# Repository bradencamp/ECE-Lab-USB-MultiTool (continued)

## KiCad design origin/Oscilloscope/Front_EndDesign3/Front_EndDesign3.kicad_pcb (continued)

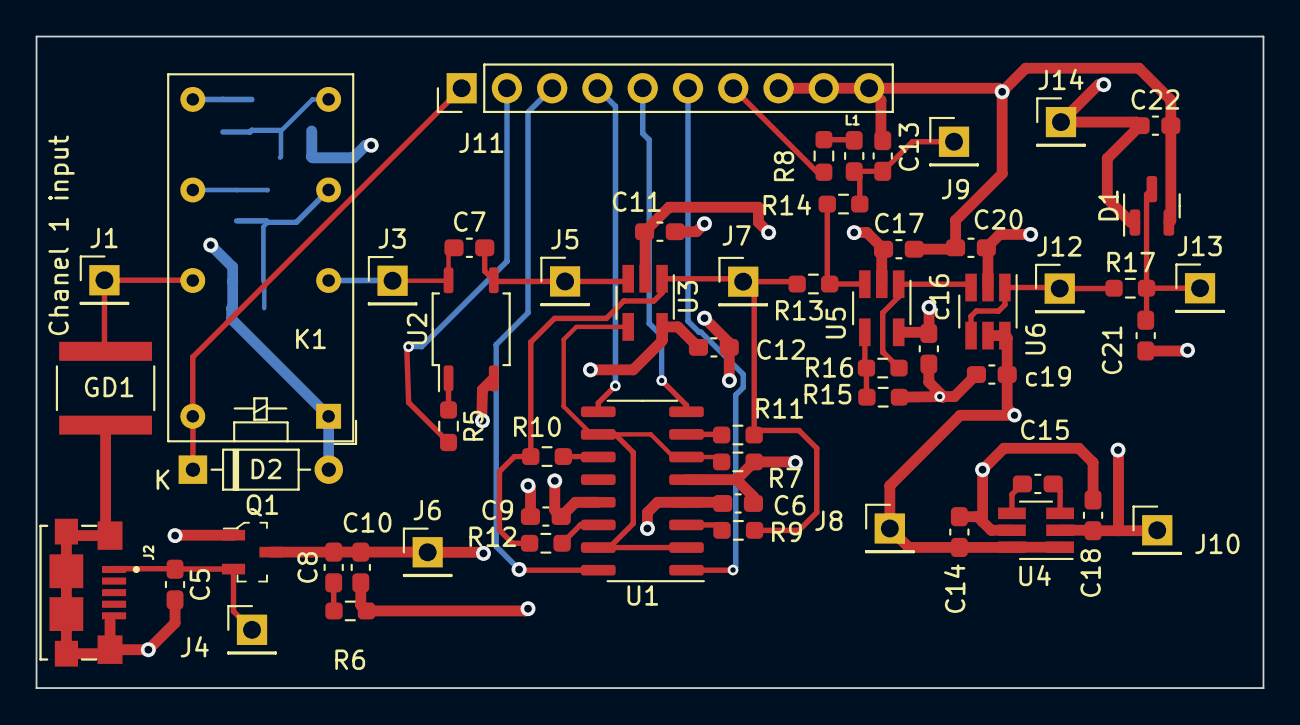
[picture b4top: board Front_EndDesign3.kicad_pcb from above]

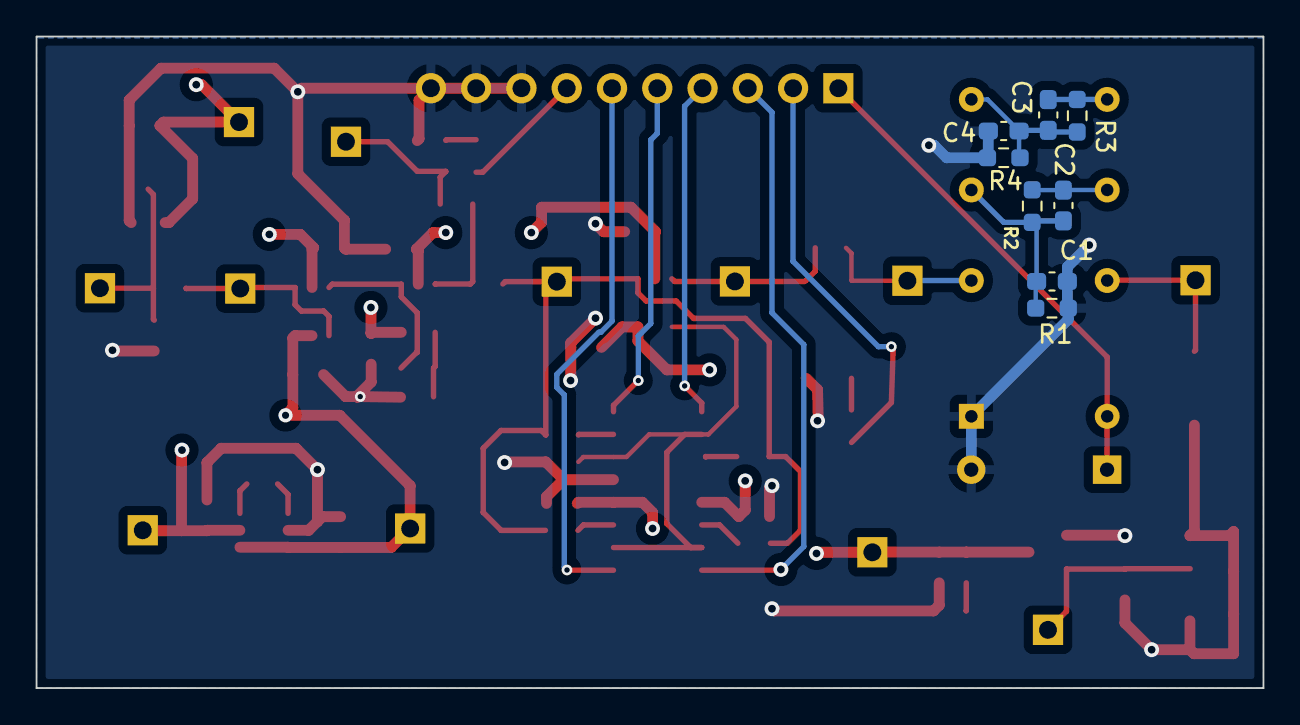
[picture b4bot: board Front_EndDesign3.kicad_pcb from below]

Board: 4 copper layers, 68.8 x 36.6 mm, 65 parts (8 on the bottom side), 36 nets.

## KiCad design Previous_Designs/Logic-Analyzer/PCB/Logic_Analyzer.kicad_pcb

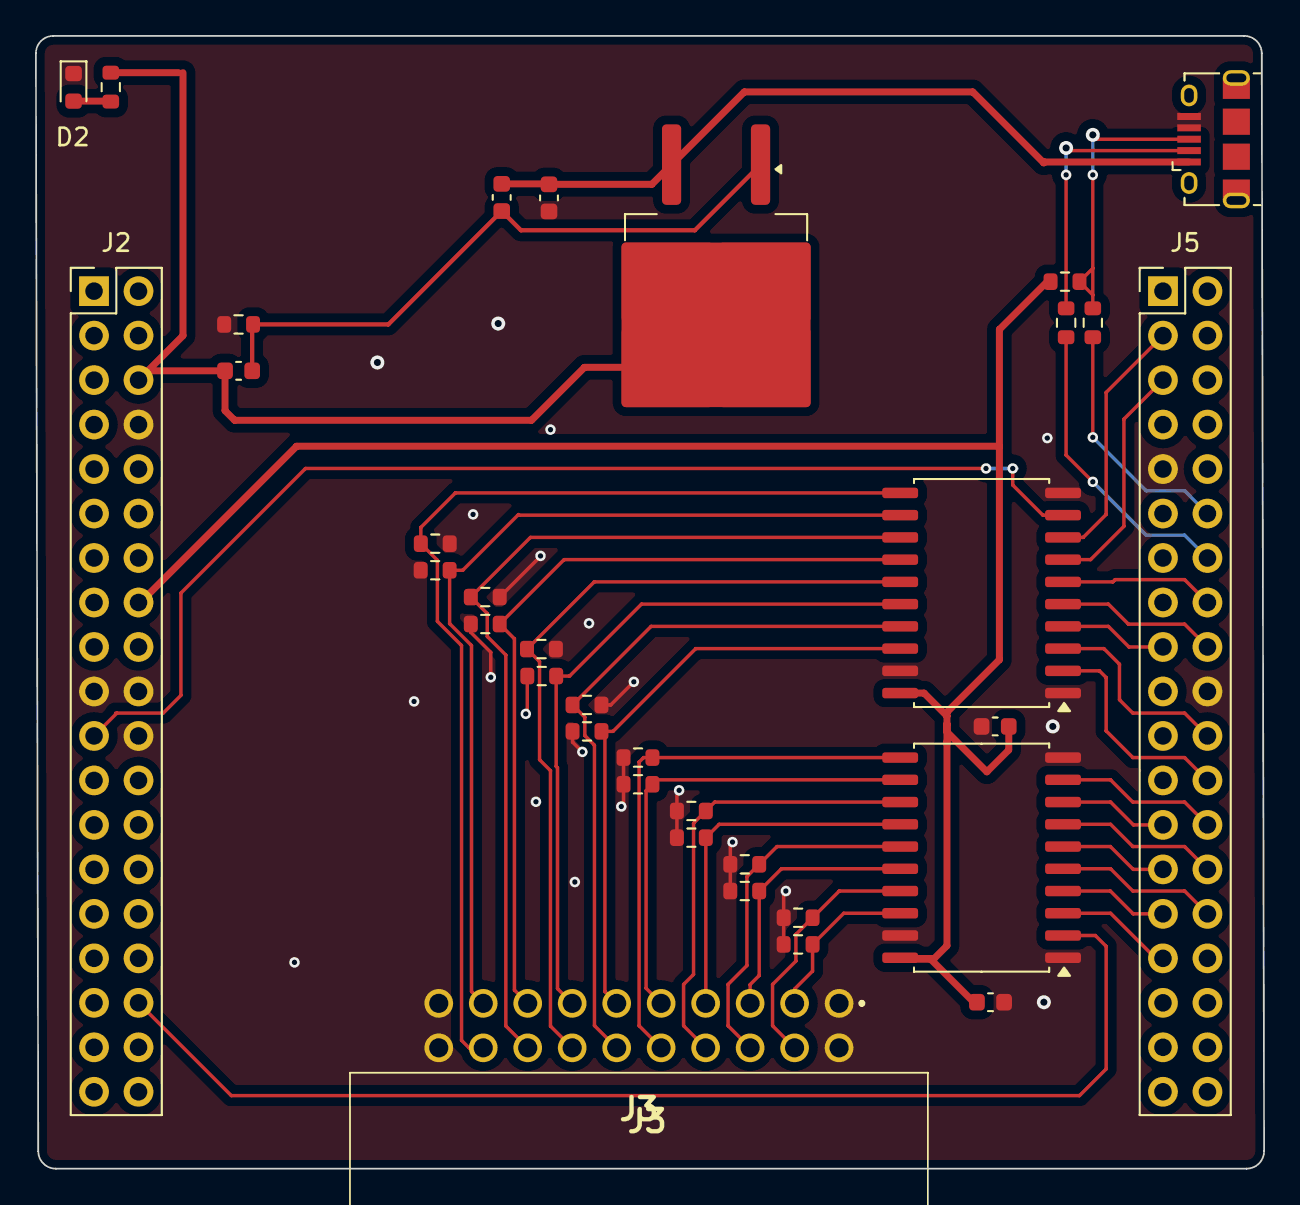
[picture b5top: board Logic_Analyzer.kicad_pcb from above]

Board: 2 copper layers, 70.1 x 64.7 mm, 34 parts (0 on the bottom side), 42 nets.

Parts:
C1, C2, C4, C5: 100nF; C_0603_1608Metric
C3: 1uF; C_0603_1608Metric
D2: LED; LED_0603_1608Metric
J1: USB Micro; USB_Micro-B_Amphenol_10118194_Horizontal
J2: nuc303_LEFT; PinSocket_2x19_P2.54mm_Vertical
J3: 30320-5002HB; 303205002HB
J5: nuc303_RIGHT; PinSocket_2x19_P2.54mm_Vertical
Q2: PMOS; TO-263-2
R1, R6, R7, R8, R9, R10, R11, R12, R13, R14, R15, R16, R17, R18, R19, R20, R21: 1M; R_0603_1608Metric
R2, R4: 22; R_0603_1608Metric
R3: 1k; R_0603_1608Metric
R5: 1.5k; R_0603_1608Metric
U1, U3: 74HC245N; SOIC-20W_7.5x12.8mm_P1.27mm

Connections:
+3V3: C4.1, C5.2, J2.16 (3V3), R5.2, U1.20 (VCC), U3.20 (VCC)
+5V: C2.1, J2.6 (E5V), Q2.2 (G), R3.1
/D+: J1.3 (D+), R2.2, R5.1
/D-: J1.2 (D-), R4.1
/PB0: J2.34 (PB0), U1.2 (A0)
/PB1: J5.24 (PB1), U3.2 (A0)
/PB2: J5.22 (PB2), U3.3 (A1)
/PB3: J5.31 (PB3), U1.3 (A1)
/PB4: J5.27 (PB4), U1.6 (A4)
/PB5: J5.29 (PB5), U1.4 (A2)
/PB6: J5.17 (PB6), U3.4 (A2)
/PB7: J2.21 (PB7), U3.9 (A7)
/PB8: J5.3 (PB8), U3.8 (A6)
/PB9: J5.5 (PB9), U3.7 (A5)
/PB10: J5.25 (PB10), U1.8 (A6)
/PB11: J5.18 (PB11), U3.5 (A3)
/PB12: J5.16 (PB12), U3.6 (A4)
/PB13: J5.30 (PB13), U1.5 (A3)
/PB14: J5.28 (PB14), U1.7 (A5)
/PB15: J5.26 (PB15), U1.9 (A7)
/VBUS: C1.1, C3.1, J1.1 (VBUS), Q2.3 (S)
GND: C3.2, C4.2, C5.1, D2.1 (K), J1.4 (GND), J1.5 (Shield), J2.8 (GND), J2.19 (GND), J2.20 (GND), J2.22 (GND), J3.1, J3.2, J3.19, J3.20, J5.9 (GND), J5.20 (GND), R1.2, R6.1, R7.2, R8.1, R9.2, R10.1, R11.2, R12.2, R13.1, R14.2, R15.2, R16.2, R17.2, R18.1, R19.1, R20.1, R21.1, U1.1 (DIR), U1.10 (GND), U1.19 (~OE), U3.1 (DIR), U3.10 (GND), U3.19 (~OE)
unnamed: D2.2 (A), R3.2
unnamed: J5.14 (PA11), R4.2
unnamed: J5.12 (PA12), R2.1
unnamed: C1.2, C2.2, Q2.1 (D), R1.1
unnamed: J3.3, R14.1, U1.18 (B0)
unnamed: J3.4, R18.2, U1.17 (B1)
unnamed: J3.5, R15.1, U1.16 (B2)
unnamed: J3.6, R19.2, U1.15 (B3)
unnamed: J3.7, R16.1, U1.14 (B4)
unnamed: J3.8, R21.2, U1.13 (B5)
unnamed: J3.9, R17.1, U1.12 (B6)
unnamed: J3.10, R20.2, U1.11 (B7)
unnamed: J3.11, R12.1, U3.18 (B0)
unnamed: J3.12, R8.2, U3.17 (B1)
unnamed: J3.13, R9.1, U3.16 (B2)
unnamed: J3.14, R13.2, U3.15 (B3)
unnamed: J3.15, R11.1, U3.14 (B4)
unnamed: J3.16, R10.2, U3.13 (B5)
unnamed: J3.17, R7.1, U3.12 (B6)
unnamed: J3.18, R6.2, U3.11 (B7)

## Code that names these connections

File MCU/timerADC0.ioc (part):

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Mcu.Name=STM32H563ZITx
Mcu.Package=LQFP144
Mcu.UserName=STM32H563ZITx
PA0.Signal=ADCx_INP0
PA1.GPIOParameters=GPIO_Speed,GPIO_PuPd,GPIO_Label,GPIO_Mode
PA1.GPIO_Label=RMII_REF_CLK
PA1.GPIO_Mode=GPIO_MODE_AF_PP
PA1.GPIO_PuPd=GPIO_NOPULL
PA1.GPIO_Speed=GPIO_SPEED_FREQ_LOW
PA1.Signal=ETH_REF_CLK
PA11.GPIOParameters=GPIO_Label
PA11.GPIO_Label=USB_FS_N
PA11.Mode=Device
PA11.Signal=USB_DM
PA12.GPIOParameters=GPIO_Label
PA12.GPIO_Label=USB_FS_P
PA12.Mode=Device
PA12.Signal=USB_DP
PA13(JTMS/SWDIO).GPIOParameters=GPIO_Label
PA13(JTMS/SWDIO).GPIO_Label=SWDIO
PA13(JTMS/SWDIO).Signal=DEBUG_JTMS-SWDIO
PA14(JTCK/SWCLK).GPIOParameters=GPIO_Label
PA14(JTCK/SWCLK).GPIO_Label=SWCLK
PA14(JTCK/SWCLK).Signal=DEBUG_JTCK-SWCLK
PA15(JTDI).GPIOParameters=GPIO_Label
PA15(JTDI).GPIO_Label=T_JTDI
PA15(JTDI).Signal=DEBUG_JTDI
PA2.GPIOParameters=GPIO_Speed,GPIO_PuPd,GPIO_Label,GPIO_Mode
PA2.GPIO_Label=RMII_MDIO
PA2.GPIO_Mode=GPIO_MODE_AF_PP
PA2.GPIO_PuPd=GPIO_NOPULL
PA2.GPIO_Speed=GPIO_SPEED_FREQ_LOW
PA2.Signal=ETH_MDIO
PA4.Signal=COMP_DAC11_group
PA5.Signal=COMP_DAC12_group
PA6.Signal=ADCx_INP3
PA7.Signal=ETH_CRS_DV
PA9.GPIOParameters=GPIO_Label
PA9.GPIO_Label=UCDP_DBn
PA9.Signal=UCPD1_DB1
PB0.Signal=GPIO_Output
PB10.GPIOParameters=GPIO_Label
PB10.GPIO_Label=CH2_1\:5_AMP
PB10.Signal=GPIO_Output
PB13.GPIOParameters=GPIO_Label
PB13.GPIO_Label=UCPD_CC1
PB13.Signal=UCPD1_CC1
PB14.GPIOParameters=GPIO_Label
PB14.GPIO_Label=UCPD_CC2
PB14.Signal=UCPD1_CC2
PB15.GPIOParameters=GPIO_Speed,GPIO_PuPd,GPIO_Label,GPIO_Mode
PB15.GPIO_Label=RMII_TXD1
PB15.GPIO_Mode=GPIO_MODE_AF_PP
PB15.GPIO_PuPd=GPIO_NOPULL
PB15.GPIO_Speed=GPIO_SPEED_FREQ_LOW
PB15.Signal=ETH_TXD1
PB3(JTDO/TRACESWO).GPIOParameters=GPIO_Label
PB3(JTDO/TRACESWO).GPIO_Label=SWO
PB3(JTDO/TRACESWO).Signal=DEBUG_JTDO-SWO
PB6.GPIOParameters=GPIO_Label
PB6.GPIO_Label=ARD_D1_TX
PB6.Signal=LPUART1_TX
PB7.GPIOParameters=GPIO_Label
PB7.GPIO_Label=ARD_D0_RX
PB7.Signal=LPUART1_RX
PC1.GPIOParameters=GPIO_Speed,GPIO_PuPd,GPIO_Label,GPIO_Mode
PC1.GPIO_Label=RMII_MDC
PC1.GPIO_Mode=GPIO_MODE_AF_PP
PC1.GPIO_PuPd=GPIO_NOPULL
PC1.GPIO_Speed=GPIO_SPEED_FREQ_LOW
PC1.Signal=ETH_MDC
PC10.GPIOParameters=GPIO_Label
PC10.GPIO_Label=CH1_1\:1_AMP
PC10.Signal=GPIO_Output
PC11.GPIOParameters=GPIO_Label
PC11.GPIO_Label=CH1_1\:2.5_AMP
PC11.Signal=GPIO_Output
PC12.GPIOParameters=GPIO_Label
PC12.GPIO_Label=CH1_1\:5_AMP
PC12.Signal=GPIO_Output
PC13.Signal=GPIO_Input
PC14-OSC32_IN(OSC32_IN).Mode=LSE-External-Oscillator
PC14-OSC32_IN(OSC32_IN).Signal=RCC_OSC32_IN
PC15-OSC32_OUT(OSC32_OUT).Mode=LSE-External-Oscillator
PC15-OSC32_OUT(OSC32_OUT).Signal=RCC_OSC32_OUT
PC4.GPIOParameters=GPIO_Speed,GPIO_PuPd,GPIO_Label,GPIO_Mode
PC4.GPIO_Label=RMII_RXD0
PC4.GPIO_Mode=GPIO_MODE_AF_PP
PC4.GPIO_PuPd=GPIO_NOPULL
PC4.GPIO_Speed=GPIO_SPEED_FREQ_LOW
PC4.Signal=ETH_RXD0
PC5.GPIOParameters=GPIO_Speed,GPIO_PuPd,GPIO_Label,GPIO_Mode
PC5.GPIO_Label=RMII_RXD1
PC5.GPIO_Mode=GPIO_MODE_AF_PP
PC5.GPIO_PuPd=GPIO_NOPULL
PC5.GPIO_Speed=GPIO_SPEED_FREQ_LOW
PC5.Signal=ETH_RXD1
PC6.Signal=S_TIM3_CH1
PC7.Signal=S_TIM3_CH2
PC8.Signal=S_TIM8_CH3
PD0.GPIOParameters=GPIO_Label
PD0.GPIO_Label=CH1_1\:10_AMP
PD0.Signal=GPIO_Output
PD1.GPIOParameters=GPIO_Label
PD1.GPIO_Label=CH1_ATTENUATOR
PD1.Signal=GPIO_Output
PD2.GPIOParameters=GPIO_Label
PD2.GPIO_Label=CH1_AC/DC
PD2.Signal=GPIO_Output
PD4.GPIOParameters=GPIO_Label
PD4.GPIO_Label=External LED0
PD4.Signal=GPIO_Output
PD5.GPIOParameters=GPIO_Label
PD5.GPIO_Label=External LED1
PD5.Signal=GPIO_Output
PD6.GPIOParameters=GPIO_Label
PD6.GPIO_Label=External LED2
PD6.Signal=GPIO_Output
PD7.GPIOParameters=GPIO_Label
PD7.GPIO_Label=External LED3
PD7.Signal=GPIO_Output
PD8.Signal=USART3_TX
PD9.Signal=USART3_RX
PE11.Signal=S_TIM1_CH2
PE12.GPIOParameters=GPIO_Label
PE12.GPIO_Label=GAIN_C1
PE12.Signal=GPIO_Output
PE13.GPIOParameters=GPIO_Label
PE13.GPIO_Label=GAIN_C0
PE13.Signal=GPIO_Output
PE14.GPIOParameters=GPIO_Label
PE14.GPIO_Label=CH2_1\:1_AMP
PE14.Signal=GPIO_Output
PE15.GPIOParameters=GPIO_Label
PE15.GPIO_Label=CH2_1\:2.5_AMP
PE15.Signal=GPIO_Output
PE2.GPIOParameters=GPIO_Label
PE2.GPIO_Label=TRACE_CK
PE2.Signal=DEBUG_TRACECLK
PE3.GPIOParameters=GPIO_Label
PE3.GPIO_Label=TRACE_D0
PE3.Signal=DEBUG_TRACED0
PE4.GPIOParameters=GPIO_Label
PE4.GPIO_Label=TRACE_D1
PE4.Signal=DEBUG_TRACED1
PE5.GPIOParameters=GPIO_Label
PE5.GPIO_Label=TRACE_D2
PE5.Signal=DEBUG_TRACED2
PE6.GPIOParameters=GPIO_Label
PE6.GPIO_Label=TRACE_D3
PE6.Signal=DEBUG_TRACED3
PE7.GPIOParameters=GPIO_Label
PE7.GPIO_Label=CH2_AC/DC
PE7.Signal=GPIO_Output
PE9.Signal=S_TIM1_CH1
PF0.Signal=GPIO_Input
PF1.Signal=GPIO_Input
PF10.Signal=GPIO_Input
PF11.Signal=GPIO_Input
PF12.Signal=GPIO_Input
PF13.Signal=GPIO_Input
PF14.Signal=GPIO_Input
PF15.Signal=GPIO_Input
PF2.Signal=GPIO_Input
PF3.Signal=GPIO_Input
PF4.Signal=GPIO_Input
PF5.Signal=GPIO_Input
PF6.Signal=GPIO_Input
PF7.Signal=GPIO_Input
PF8.Signal=GPIO_Input
PF9.Signal=GPIO_Input
PG0.Signal=GPIO_Output
PG1.GPIOParameters=GPIO_Label
PG1.GPIO_Label=CH2_ATTENUATOR
PG1.Signal=GPIO_Output
PG11.GPIOParameters=GPIO_Speed,GPIO_PuPd,GPIO_Label,GPIO_Mode
PG11.GPIO_Label=RMII_TXT_EN
PG11.GPIO_Mode=GPIO_MODE_AF_PP
PG11.GPIO_PuPd=GPIO_NOPULL
PG11.GPIO_Speed=GPIO_SPEED_FREQ_LOW
PG11.Signal=ETH_TX_EN
PG13.GPIOParameters=GPIO_Speed,GPIO_PuPd,GPIO_Label,GPIO_Mode
PG13.GPIO_Label=RMI_TXD0
PG13.GPIO_Mode=GPIO_MODE_AF_PP
PG13.GPIO_PuPd=GPIO_NOPULL
PG13.GPIO_Speed=GPIO_SPEED_FREQ_LOW
PG13.Signal=ETH_TXD0
PG4.Signal=GPIO_Output
PG7.GPIOParameters=GPIO_Label
PG7.GPIO_Label=UCPD_FLT
PG7.Signal=GPXTI7
PH0-OSC_IN(PH0).GPIOParameters=GPIO_Label
PH0-OSC_IN(PH0).GPIO_Label=STLK_MCO
PH0-OSC_IN(PH0).Mode=HSE-External-Clock-Source
PH0-OSC_IN(PH0).Signal=RCC_OSC_IN
RCC.HSE_VALUE=8000000
RCC.SYSCLKFreq_VALUE=250000000
RCC.SYSCLKSource=RCC_SYSCLKSOURCE_PLLCLK
board=NUCLEO-H563ZI
boardIOC=true

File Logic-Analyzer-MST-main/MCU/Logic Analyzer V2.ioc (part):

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Mcu.Name=STM32F303R(D-E)Tx
Mcu.Package=LQFP64
Mcu.UserName=STM32F303RETx
PA11.Mode=Device
PA11.Signal=USB_DM
PA12.Mode=Device
PA12.Signal=USB_DP
PA13.GPIOParameters=GPIO_Label
PA13.GPIO_Label=TMS
PA13.Mode=Serial_Wire
PA13.Signal=SYS_JTMS-SWDIO
PA14.GPIOParameters=GPIO_Label
PA14.GPIO_Label=TCK
PA14.Mode=Serial_Wire
PA14.Signal=SYS_JTCK-SWCLK
PA5.GPIOParameters=GPIO_Speed,GPIO_PuPd,GPIO_Label,GPIO_Mode
PA5.GPIO_Label=LD2 [Green Led]
PA5.GPIO_Mode=GPIO_MODE_OUTPUT_PP
PA5.GPIO_PuPd=GPIO_NOPULL
PA5.GPIO_Speed=GPIO_SPEED_FREQ_LOW
PA5.Signal=GPIO_Output
PB0.Signal=GPIO_Input
PB1.Signal=GPIO_Input
PB10.Signal=GPIO_Input
PB11.Signal=GPIO_Input
PB12.Signal=GPIO_Input
PB13.Signal=GPIO_Input
PB14.Signal=GPIO_Input
PB15.Signal=GPIO_Input
PB2.Signal=GPIO_Input
PB3.Signal=GPIO_Input
PB4.Signal=GPIO_Input
PB5.Signal=GPIO_Input
PB6.Signal=GPIO_Input
PB7.Signal=GPIO_Input
PB8.Signal=GPIO_Input
PB9.Signal=GPIO_Input
PC13.GPIOParameters=GPIO_Label,GPIO_ModeDefaultEXTI
PC13.GPIO_Label=B1 [Blue PushButton]
PC13.GPIO_ModeDefaultEXTI=GPIO_MODE_IT_FALLING
PC13.Signal=GPXTI13
PC14-OSC32_IN.Mode=LSE-External-Oscillator
PC14-OSC32_IN.Signal=RCC_OSC32_IN
PC15-OSC32_OUT.Mode=LSE-External-Oscillator
PC15-OSC32_OUT.Signal=RCC_OSC32_OUT
PF0-OSC_IN.Mode=HSE-External-Oscillator
PF0-OSC_IN.Signal=RCC_OSC_IN
PF1-OSC_OUT.Mode=HSE-External-Oscillator
PF1-OSC_OUT.Signal=RCC_OSC_OUT
RCC.HSE_VALUE=8000000
RCC.SYSCLKFreq_VALUE=72000000
RCC.SYSCLKSourceVirtual=RCC_SYSCLKSOURCE_PLLCLK
board=NUCLEO-F303RE
boardIOC=true

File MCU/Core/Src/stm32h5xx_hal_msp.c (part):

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
    __HAL_RCC_GPIOA_CLK_ENABLE();
    /**ADC1 GPIO Configuration
    PA0     ------> ADC1_INP0
    */
    GPIO_InitStruct.Pin = GPIO_PIN_0;
    GPIO_InitStruct.Mode = GPIO_MODE_ANALOG;
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
    __HAL_RCC_GPIOA_CLK_ENABLE();
    /**ADC2 GPIO Configuration
    PA6     ------> ADC2_INP3
    */
    GPIO_InitStruct.Pin = GPIO_PIN_6;
    GPIO_InitStruct.Mode = GPIO_MODE_ANALOG;
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    }

    /**ADC1 GPIO Configuration
    PA0     ------> ADC1_INP0
    */
    HAL_GPIO_DeInit(GPIOA, GPIO_PIN_0);

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    }

    /**ADC2 GPIO Configuration
    PA6     ------> ADC2_INP3
    */
    HAL_GPIO_DeInit(GPIOA, GPIO_PIN_6);

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
    __HAL_RCC_GPIOA_CLK_ENABLE();
    /**DAC1 GPIO Configuration
    PA4     ------> DAC1_OUT1
    PA5     ------> DAC1_OUT2
    */
    GPIO_InitStruct.Pin = GPIO_PIN_4|GPIO_PIN_5;
    GPIO_InitStruct.Mode = GPIO_MODE_ANALOG;
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    __HAL_RCC_DAC1_CLK_DISABLE();

    /**DAC1 GPIO Configuration
    PA4     ------> DAC1_OUT1
    PA5     ------> DAC1_OUT2
    */
    HAL_GPIO_DeInit(GPIOA, GPIO_PIN_4|GPIO_PIN_5);

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  /* USER CODE END TIM1_MspPostInit 0 */
    __HAL_RCC_GPIOE_CLK_ENABLE();
    /**TIM1 GPIO Configuration
    PE9     ------> TIM1_CH1
    PE11     ------> TIM1_CH2
    */
    GPIO_InitStruct.Pin = GPIO_PIN_9|GPIO_PIN_11;
    GPIO_InitStruct.Mode = GPIO_MODE_AF_PP;
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
    __HAL_RCC_GPIOC_CLK_ENABLE();
    /**TIM3 GPIO Configuration
    PC6     ------> TIM3_CH1
    PC7     ------> TIM3_CH2
    */
    GPIO_InitStruct.Pin = GPIO_PIN_6|GPIO_PIN_7;
    GPIO_InitStruct.Mode = GPIO_MODE_AF_PP;
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
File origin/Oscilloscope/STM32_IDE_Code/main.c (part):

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  GPIO_InitStruct.Pull = GPIO_NOPULL;
  HAL_GPIO_Init(B1_GPIO_Port, &GPIO_InitStruct);

  /*Configure GPIO pins : LD2_Pin PA8 PA9 PA10 */
  GPIO_InitStruct.Pin = LD2_Pin|GPIO_PIN_8|GPIO_PIN_9|GPIO_PIN_10;
  GPIO_InitStruct.Mode = GPIO_MODE_OUTPUT_PP;
  GPIO_InitStruct.Pull = GPIO_NOPULL;
  GPIO_InitStruct.Speed = GPIO_SPEED_FREQ_LOW;
  HAL_GPIO_Init(GPIOA, &GPIO_InitStruct);

  /*Configure GPIO pins : PB10 PB4 */
  GPIO_InitStruct.Pin = GPIO_PIN_10|GPIO_PIN_4;
  GPIO_InitStruct.Mode = GPIO_MODE_OUTPUT_PP;
  GPIO_InitStruct.Pull = GPIO_NOPULL;
  GPIO_InitStruct.Speed = GPIO_SPEED_FREQ_LOW;
  HAL_GPIO_Init(GPIOB, &GPIO_InitStruct);

  /*Configure GPIO pin : PC7 */
  GPIO_InitStruct.Pin = GPIO_PIN_7;
  GPIO_InitStruct.Mode = GPIO_MODE_OUTPUT_PP;
  GPIO_InitStruct.Pull = GPIO_NOPULL;
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
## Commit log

2024-09-12 Updated GUI readme syntax
2024-09-23 Code cleanup
2024-10-18 Figuring out USB
    Have to use ThreadX RTOS and USBX to implement USB function. This is just the first way I got working.
2024-10-18 USB attempt
    Have to use ThreadX RTOS and USBX.
2024-10-18 Initial GUI
2024-10-23 2 ADCs using DMA to transfer over USART
    Just a test
2024-10-23 Moved layouts into individual functions, collapsed AWG panel
2024-10-29 Labeled text widget and initial graph
2024-10-29 Starting PCB schematics
2024-10-31 Bare Metal USB
    spams "hello" on COM12. Cannot use ICACHE.
2024-10-31 GUI layout and updating random graph
2024-11-01 added missing GND
2024-11-01 testing new branch
2024-11-01 inital branch
2024-11-05 DAC + USB
    Based on previous team's work.
2024-11-06 awg checkboxes work with live plotting, but need to fix waveform positioning for displaying individual chanels. Placement correct for simultaneous channels
2024-11-12 run/stop button works, updated trigger mode options
2024-11-13 minor changes & added comments. still trying to get scope channel checkboxes working
2024-11-13 AWG control for ch1 and time divs. Also now working with numpy over python lists
2024-11-13 minor changes
2024-11-14 combined brach code into 1 file. added ch2 sine wave, removed temperature test wave
2024-11-15 added 8 example square waves for logic analyzer. checkboxes for analyzer & scope buggy, working on fixing
2024-11-16 Starting PCB layout
2024-11-18 Finished PCB traces
2024-12-03 Waveform Type selector completed
2024-12-04 Simple serial connection and color correction
2024-12-04 Update PCB
2024-12-07 began merging handlers for boxes, buttons, plot, user input; added ch2 for all; minor text/design changes; will update colors
2024-12-17 fixed ch2 awg amplitude input box. live input for amp. now works for both channels & plot autoscales correctly
2024-12-17 removed old commit comments
2025-01-06 Updated PCB Layout 1.2
2025-01-07 Revert "Updated PCB Layout 1.2"
    This reverts commit d1c1e699940df8d57e662003311594f1cc4f50c6.
    Reverting broken commit
2025-01-07 Moving files to where they should be
2025-01-15 interim update (not done)
2025-01-17 Routed revised PCB
2025-01-17 fix name for PWR_FLAG
2025-01-24 current local copy. will discuss w/ erick today
2025-02-05 update components and wiring
2025-02-11 change USB design and MCU
2025-02-11 AWG working
    Use the AWG team's GUI to interact with the MCU.
2025-02-11 Add files via upload
    Used AWG team GUI to test. For AWG GUI VID and PID need to be modified in connection.py to establish connection. (port.vid == 1155 and port.pid == 22352)
2025-02-12 Modified to function simmilarly to amai8 branch.
2025-02-16 update MCU and USB, fix some footprints
2025-02-18 modify MCU and name tags
2025-02-19 add usb protection
2025-02-19 combined eorella & amai8 latest commits
2025-02-21 add NRST button and change MCU pins as latest
2025-02-23 Fixed up footprints
2025-02-23 Added files to gitignore
2025-02-23 Added file to gitignore
2025-02-23 Rm old libraries
2025-02-23 Started adding 20pin
2025-02-26 Began on logic analyizer. Also added csv of sample i2c connection
2025-02-26 add Logic Analyzer and finish pins
    Add Logic Analyzer. Add separate pins to 20 pins input(logic and scope) and 4 pins output(AWG). Add 4 programing pins.
2025-02-26 minor fixes
2025-02-26 footprint with minor fixes
2025-02-28 updated csv functionality
2025-03-01 rearrange logic pins, connectors, fix some name tags
2025-03-01 Updated schematic
2025-03-01 Update logic analyzer schematic
2025-03-01 change 3.3V regulator
    Using ST1L05APU33R instead of ST1L05CPU33R for simplicity and save of sanity
2025-03-01 Updated schematic and PCB
2025-03-01 update ST1L05APU33R schematic
2025-03-01 update switch name
2025-03-01 swap MCU pins for routing
2025-03-02 starting the layout again
2025-03-05 continue PCB layout
2025-03-06 Update pcb layout
2025-03-06 some very small wirings, and layout
2025-03-08 Updated pcb
2025-03-10 Updated pcb layout again
2025-03-10 Finished PCB layout
2025-03-11 fix the pin out
    never be lazy and stupid at the same time 👎
2025-03-12 rearrange pins
2025-03-12 fixed the mosfet1 routing(I hope)
    route->interactive router settings
    choose highlight collisions, allow DRC violations.
2025-03-12 change mosfet footprint
2025-03-12 Continued work on Logic analyzer. Removed manuall set tick spacing and added focus line
2025-03-15 fixed grounds for several components and fix 5V clean
2025-03-16 fix board wiring as mentioned in email by Prof. Kaps
    This is the follow up, wiring, of the previous schematic fix.
2025-03-17 final version prototype
2025-03-18 change scope diode footprint
2025-03-18 updated w/ eorella latest commit. added 8 logic analyzer test signals. working on fixing widget spacing
2025-03-18 Added holes to PCB schematic, fixed DRC
2025-03-19 some more minor PCB changes
2025-03-19 fix footprint and change button
2025-03-19 v/div scope ranges roughly working. needs to be fine tuned
2025-03-19 AWG Barely working
    Very very basic implementation of AWG.
2025-03-20 PCB updates from meeting 3/19
2025-03-20 fixed AWG pins to MCU
2025-03-21 just add a note
2025-03-21 fix parameters
2025-03-22 change USB footprint, fix some warnings and problems
2025-03-23 Resolved DRC/ERC errors in PCB and schematic
2025-03-23 update gitignore
2025-03-23 clean up ZIPs of duplicate files
2025-03-23 Add missing backups back from onedrive
2025-03-24 put the h563 schematic in Git for easy access
2025-03-24 Revert 4705375 - H563 schematic is already in PCB/USBLabTool/library
    This reverts commit 4705375741c8b330ebbcd11db5d307989b1aad29.
2025-03-25 rename files
2025-03-25 replace xml files
2025-03-25 AWG
    AWG works, connection works but just needs to changed a bit so it doesnt appear to take so long to connect, basics of oscilloscope
2025-03-25 oscilloscope and awg
2025-03-26 moved graphs to own setup function, also started preparation to separate AWG and OSC
2025-03-26 Added second Y-axis to osc graph
2025-04-02 Timer based oscilloscope
2025-04-02 Verrrry rudimentary oscilloscope functionality
2025-04-02 New time div formation
2025-04-02 current version
2025-04-08 initial filter for STM vid when finding serial ports
2025-04-09 Initial osc graphing
2025-04-09 Post-meeting form 04/09
2025-04-10 Theoretically should theoretically work
2025-04-10 Revert "Update USBLabTool.kicad_pro"
    This reverts commit 9e4efc68bbba3a8d3bd55ee6cfff31f6e2d6ade6.
2025-04-10 updated after mtg 4/10
2025-04-12 fixes
2025-04-12 push new layout
2025-04-12 pcb update
2025-04-12 pcb updates
2025-04-13 change MCU pads and add ground planes and power planes
2025-04-13 reposition a few things
2025-04-13 nearly finish MCU, need checking, and unfinished logic analyzer
2025-04-13 try to do logic analyzer
2025-04-13 clean up layout and create space for logic analyzer
    check discord for new MCU pins
2025-04-13 V2 fixed
2025-04-14 PCB V2 updates
2025-04-14 add pads for 32kHz crystal
2025-04-14 update PCB v2 caps
2025-04-14 update pcb v2
2025-04-14 update footprint
2025-04-15 Small documentation for Graphical GUI
2025-04-16 Volts per div resonably implemented
2025-04-16 Create t
2025-04-16 logic analyzer, oscilloscope, waveform generator
    Theoretically all of these work
2025-04-16 expanded on logic analyzer, untested
2025-04-17 Time div implementation
2025-04-19 pcb v1 final
2025-04-28 Final condition of GUI
